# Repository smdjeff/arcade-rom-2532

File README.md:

# Vintage 2532 arcade ROM programmer for Raspberry Pi

* Most ROM programmers that support vintage ROMs require old PC hardware and interfaces like ISA, LPT ports that are no longer readily available.
* USB based programmers like the TL866 don't support the high voltages, long programming cycles and high currents required of vintage EEPROMs.

* Convenient Raspberry Pi Hat style form factor.
* Uses an eight bit shift register as both an IO expander and 5V level shifter to interface ROM address lines. 
* A real bi-directional level shifter for the ROM's data pins.
* An analog mux supporting the ROM's full high voltages and current.
* Simple C driver program used directly on the Pi's command line.
* [Smart single-byte retry algorithm](https://www.youtube.com/watch?v=HBokTF31uQM) accounts for difficult to program adddresses and lower VPP voltages.
* Supports several vintage classic arcade machine ROMs - like those in Space Invaders, Donkey Kong and Pacman.

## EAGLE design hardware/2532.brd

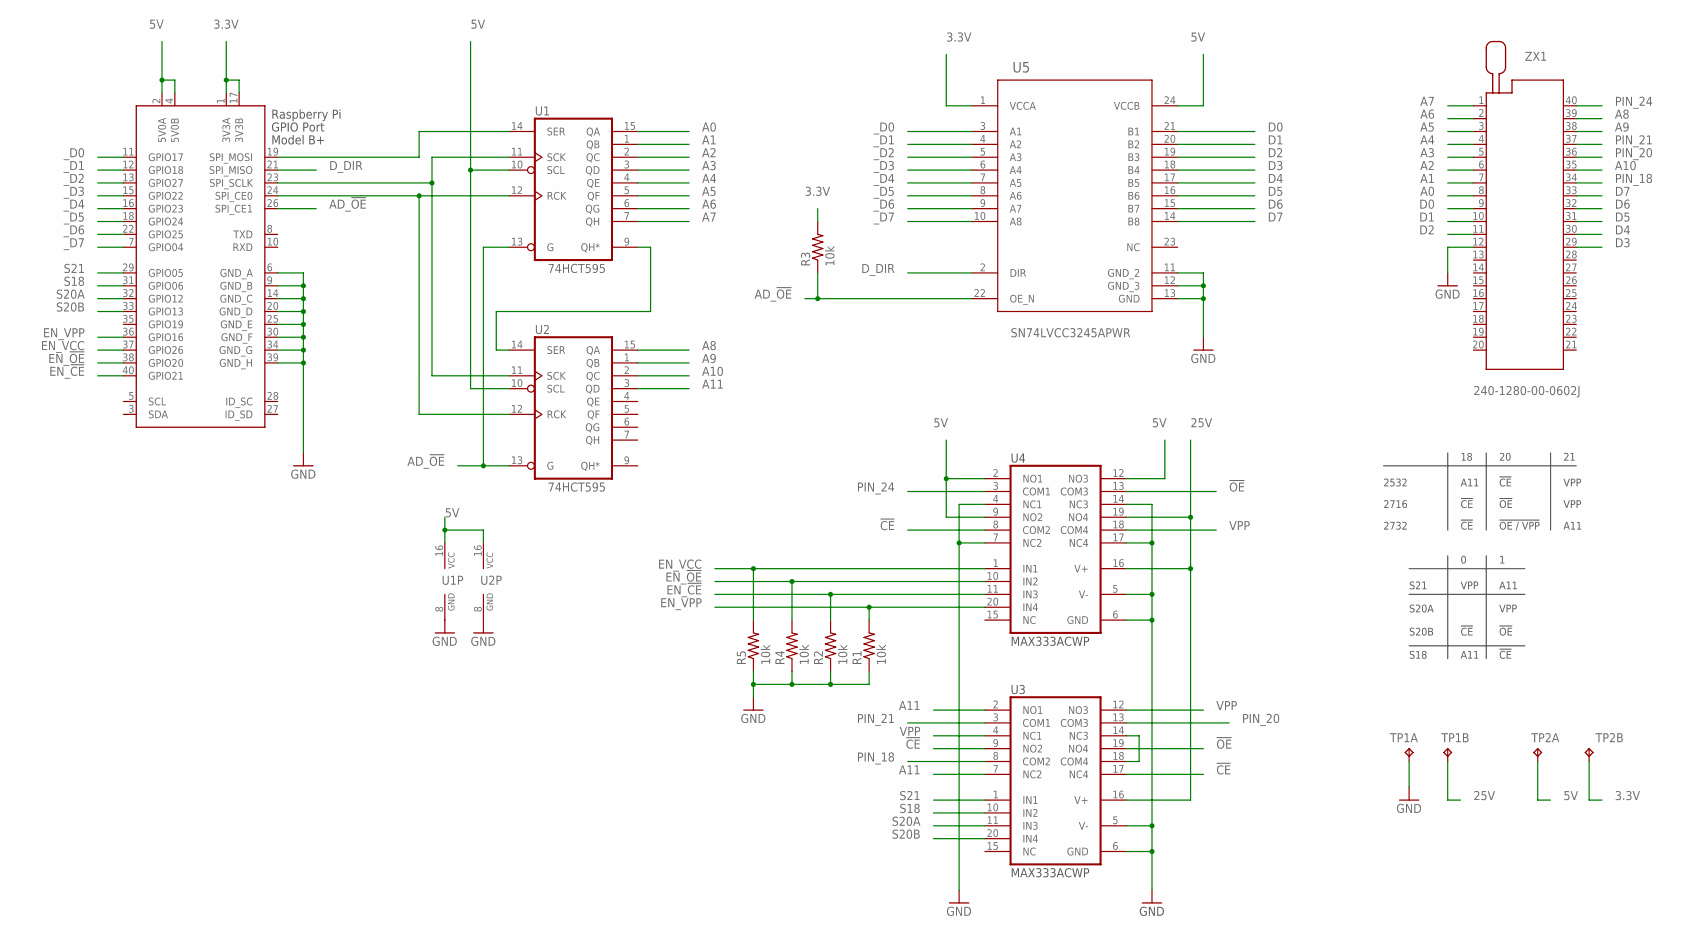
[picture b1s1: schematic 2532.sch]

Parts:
R1, R2, R3, R4, R5: 10k; R0603
TP1, TP2: TP2P2-38-17; P2-38-17
U1, U2: 74HCT595; SO16
U3, U4: MAX333ACWP; SO20L
U5: Value; PW0024A_N
X2: RASPI_BOARD_B+#_E4P; RASPI_BOARD_B+_EDGES_4DRILL_PAD
ZX1: 240-1280-00-0602J

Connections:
3.3V: R3.2, TP2.TP-2, U5.1 (VCCA), X2.1 (3V3A), X2.17 (3V3B)
5V: TP2.TP-1, U1.10 (SCL), U1.16 (VCC), U2.10 (SCL), U2.16 (VCC), U4.2 (NO1), U4.9 (NO2), U4.12 (NO3), U5.24 (VCCB), X2.2 (5V0A), X2.4 (5V0B)
25V: TP1.TP-2, U3.16 (V+), U4.16 (V+), U4.19 (NO4)
!CE: U3.9 (NO2), U3.17 (NC4), U4.8 (COM2)
!OE: U3.19 (NO4), U4.13 (COM3)
A0: U1.15 (QA), ZX1.8
A1: U1.1 (QB), ZX1.7
A2: U1.2 (QC), ZX1.6
A3: U1.3 (QD), ZX1.5
A4: U1.4 (QE), ZX1.4
A5: U1.5 (QF), ZX1.3
A6: U1.6 (QG), ZX1.2
A7: U1.7 (QH), ZX1.1
A8: U2.15 (QA), ZX1.39
A9: U2.1 (QB), ZX1.38
A10: U2.2 (QC), ZX1.35
A11: U2.3 (QD), U3.2 (NO1), U3.7 (NC2)
AD_!OE: R3.1, U1.13 (G), U2.13 (G), U5.22 (OE_N), X2.26 (SPI_CE1)
D0: U5.21 (B1), ZX1.9
D1: U5.20 (B2), ZX1.10
D2: U5.19 (B3), ZX1.11
D3: U5.18 (B4), ZX1.29
D4: U5.17 (B5), ZX1.30
D5: U5.16 (B6), ZX1.31
D6: U5.15 (B7), ZX1.32
D7: U5.14 (B8), ZX1.33
D_DIR: U5.2 (DIR), X2.21 (SPI_MISO)
EN_!CE: R2.2, U4.11 (IN3), X2.40 (GPIO21)
EN_!OE: R4.2, U4.10 (IN2), X2.38 (GPIO20)
EN_VCC: R5.2, U4.1 (IN1), X2.37 (GPIO26)
EN_VPP: R1.2, U4.20 (IN4), X2.36 (GPIO16)
GND: R1.1, R2.1, R4.1, R5.1, TP1.TP-1, U1.8 (GND), U2.8 (GND), U3.5 (V-), U3.6 (GND), U4.4 (NC1), U4.5 (V-), U4.6 (GND), U4.7 (NC2), U4.14 (NC3), U4.17 (NC4), U5.11 (GND_2), U5.12 (GND_3), U5.13 (GND), X2.6 (GND_A), X2.9 (GND_B), X2.14 (GND_C), X2.20 (GND_D), X2.25 (GND_E), X2.30 (GND_F), X2.34 (GND_G), X2.39 (GND_H), ZX1.12
unnamed: U3.14 (NC3), U3.18 (COM4)
unnamed: U1.11 (SCK), U2.11 (SCK), X2.23 (SPI_SCLK)
unnamed: U1.12 (RCK), U2.12 (RCK), X2.24 (SPI_CE0)
unnamed: U1.9 (QH*), U2.14 (SER)
unnamed: U1.14 (SER), X2.19 (SPI_MOSI)
PIN_18: U3.8 (COM2), ZX1.34
PIN_20: U3.13 (COM3), ZX1.36
PIN_21: U3.3 (COM1), ZX1.37
PIN_24: U4.3 (COM1), ZX1.40
S18: U3.10 (IN2), X2.31 (GPIO06)
S20A: U3.11 (IN3), X2.32 (GPIO12)
S20B: U3.20 (IN4), X2.33 (GPIO13)
S21: U3.1 (IN1), X2.29 (GPIO05)
VPP: U3.4 (NC1), U3.12 (NO3), U4.18 (COM4)
_D0: U5.3 (A1), X2.11 (GPIO17)
_D1: U5.4 (A2), X2.12 (GPIO18)
_D2: U5.5 (A3), X2.13 (GPIO27)
_D3: U5.6 (A4), X2.15 (GPIO22)
_D4: U5.7 (A5), X2.16 (GPIO23)
_D5: U5.8 (A6), X2.18 (GPIO24)
_D6: U5.9 (A7), X2.22 (GPIO25)
_D7: U5.10 (A8), X2.7 (GPIO04)

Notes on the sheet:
S21 S20A S20B S18
VPP !CE A11
A11 VPP !OE !CE
2532 2716 2732
!CE !OE !OE / VPP
VPP VPP A11
A11 !CE !CE

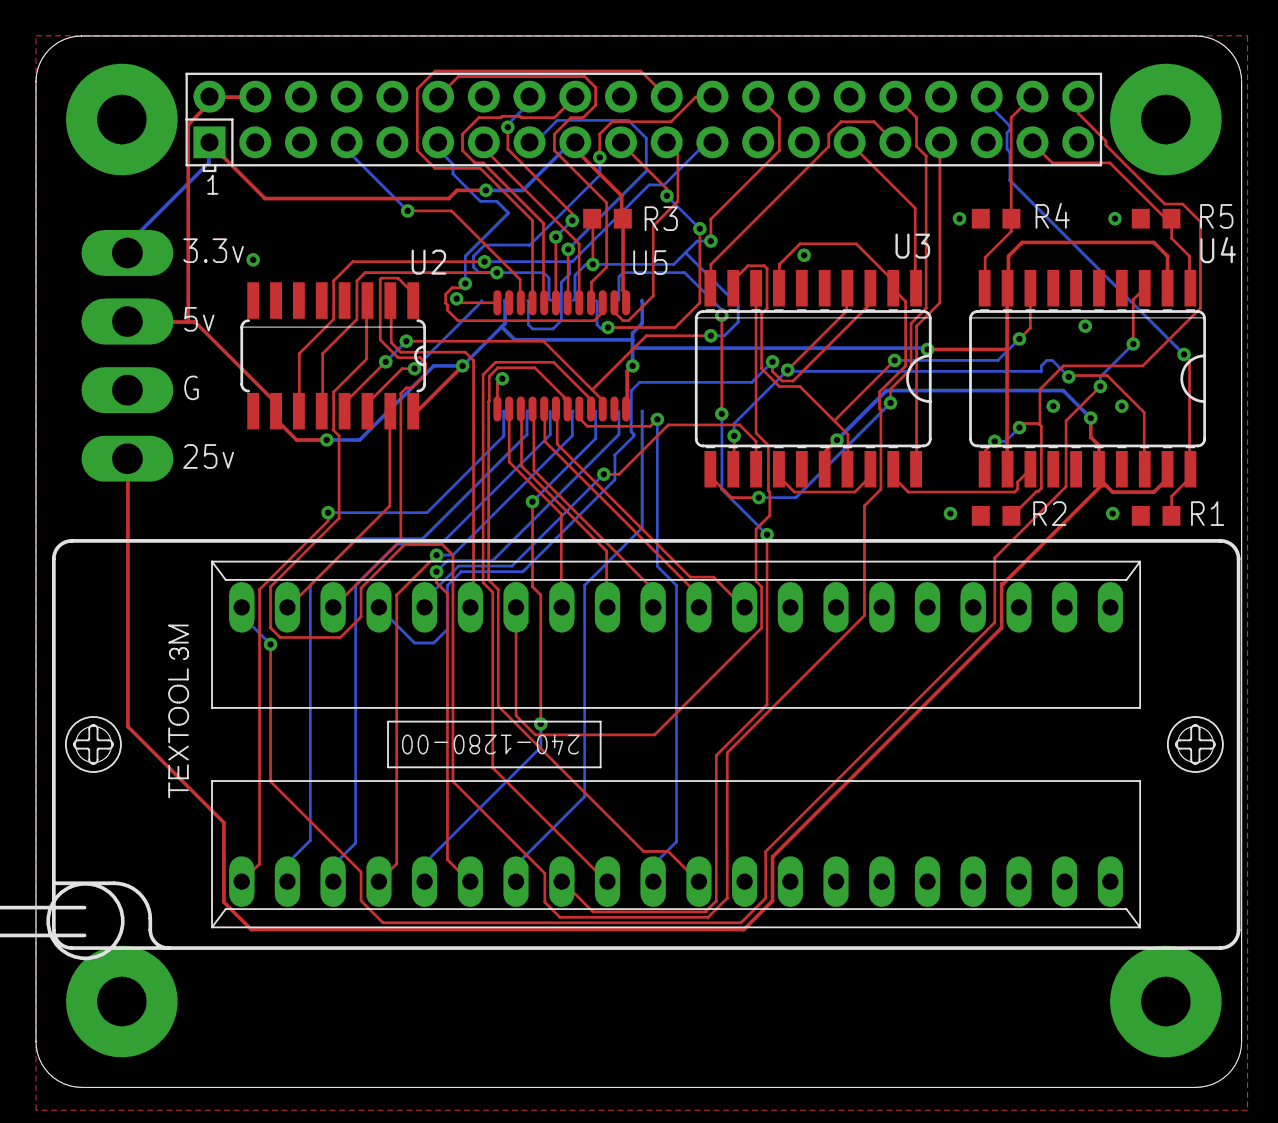
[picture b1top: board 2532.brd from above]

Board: 2 copper layers, 67.0 x 58.4 mm, 14 parts (1 on the bottom side), 54 nets.

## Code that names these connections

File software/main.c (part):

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// hack: unfortunately the MAX333 analog switch is only good
// for up to 30mA and these older EPROMs need 160mA + on VCC
// so a PNP BJT is bluewired and that's inverting VCC logic  
#define VCC(v)      do { gpioWrite( EN_VCC, !v ); } while(0)

#define VPP(v)      do { gpioWrite( EN_VPP, v ); } while(0)
#define NCE(v)      do { gpioWrite( EN_NCE, v ); } while(0)
#define NPGM(v)     do { gpioWrite( EN_NCE, v ); } while(0)
#define NOE(v)      do { gpioWrite( EN_NOE, v ); } while(0)
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            printf("2532 selected\n");
            // all pins check out
            gpioWrite( IO_S18,  0 ); // pin 18  [0:A11] 1:nCE
            gpioWrite( IO_S20A, 0 ); // pin 20  [0:20B] 1:VPP
            gpioWrite( IO_S20B, 0 ); //         [0:nCE] 1:nOE
            gpioWrite( IO_S21,  0 ); // pin 21  [0:VPP] 1:A11
            break;
        case rom2716:
            printf("2716 selected\n");
            gpioWrite( IO_S18,  1 ); // pin 18  0:A11 [1:nCE]
            gpioWrite( IO_S20A, 0 ); // pin 20  [0:20B] 1:VPP
            gpioWrite( IO_S20B, 1 ); //         0:nCE [1:nOE]
            gpioWrite( IO_S21,  0 ); // pin 21  [0:VPP] 1:A11
            break;
        case rom2732:
            printf("2732 selected\n");
            printf("warning: support for this chip is incomplete\n"); getchar();
            // A11 bad, & nCE/nOE issue?
            gpioWrite( IO_S18,  1 ); // pin 18  0:A11 [1:nCE]
            gpioWrite( IO_S20A, 1 ); // pin 20  0:20B [1:VPP]
            gpioWrite( IO_S20B, 1 ); //         0:nCE [1:nOE]
            gpioWrite( IO_S21,  1 ); // pin 21  0:VPP [1:A11]
            break;
        default:
            assert(false);
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    }
    // SN74LVCC3245 mode
    if ( mode == PI_OUTPUT ) {        
        gpioWrite( D_DIR, 1 ); // A data to B bus
    } else {
        gpioWrite( D_DIR, 0 ); // B data to A bus
    }
}

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
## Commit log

2021-03-08 Create LICENSE
2021-03-14 first pass at code
2021-03-21 specific algos for hitachi, toshiba and texas instruments flavors
2021-04-04 2532 now working
2023-04-24 add support for 2716 and pin tests
2023-04-28 support 2176
